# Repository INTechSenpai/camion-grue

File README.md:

# Après le [moon rover](https://intechsenpai.github.io/moon-rover/), INTech Senpaï est fier de vous présenter son camion grue !

## INTech Senpaï

INTech Senpaï participe pour la troisième fois à la Coupe de France de Robotique. Après le succès du robot sumo et du moon rover, qui a fini 29e à la coupe 2017, nous revenons en force avec le camion grue.

## Un modèle réduit unique

Notre camion grue est un modèle réduit à l'échelle 1:16 des immenses engins qui ont bercé notre enfance. À taille réelle, il mesurerait 3×7m ! Son design avec ses six roues (dont quatre directrices et motrices), ses feux de recul, de stop, de nuit, ses clignotants, ses gyrophare, sa grue est unique : il a été entièrement conçu par notre équipe.

## Un engin de chantier autonome

Notre camion grue utilise le système Kraken de déplacement autonome, fruit de plus de trois ans de R&D d'un doctorant en intelligence artificielle. Contrairement aux voitures autonomes qui suivent simplement une route, les engins de chantier évoluent dans un environnement encombré et changeant ; trouver un chemin implique un grand nombre de manœuvres qui peuvent être difficiles à trouver, même pour un humain. C'est ce que réalise le système Kraken, qui permet au camion grue de se déplacer avec aisance sur la table de jeu qui représente assez bien ce type d'environnement.

Le système Kraken est un logiciel libre et en [libre accès](https://github.com/PFGimenez/The-Kraken-Pathfinding).

## Un concurrent à la Coupe de France

Enfin, le camion grue est également un compétiteur de la Coupe. Sa grue terminée par une pince lui permet de manipuler des cubes et de les empiler.

## Hardware

Le camion grue est équipé de quatre unités de calcul : trois Teensy pour le contrôle bas niveau et une Raspberry Pi 3+ pour Kraken. Avec ses treize capteurs _time of flight_ dont deux rotatifs, il voit tout son environnement.

On peut voir très bien un capteur _time of flight_ au centre de l'image suivante :

Le camion grue peut facilement être ouvert afin d'accéder à son électronique.

Voici une partie de l'électronique du camion. On y voit les radiateurs des ponts en H (au centre), ainsi que deux Teensy (en bas à gauche) et la Raspberry Pi (en bas). L'autre partie de l'électronique se trouve dans la grue.

## L'équipe

[Sylvain Gaultier](https://github.com/sylvaing19) est le fondateur d'INTech Senpaï, il s'occupe de la conception et de la réalisation de la mécanique et de l'électronique du camion grue. Il a également programmé les trois Teensy.

[Pierre-François Gimenez](https://github.com/PFGimenez), doctorant en intelligence artificielle, a été recruté par Sylvain pour son projet de développement d'un camion grue autonome. Il est le concepteur et le programmeur du système Kraken.

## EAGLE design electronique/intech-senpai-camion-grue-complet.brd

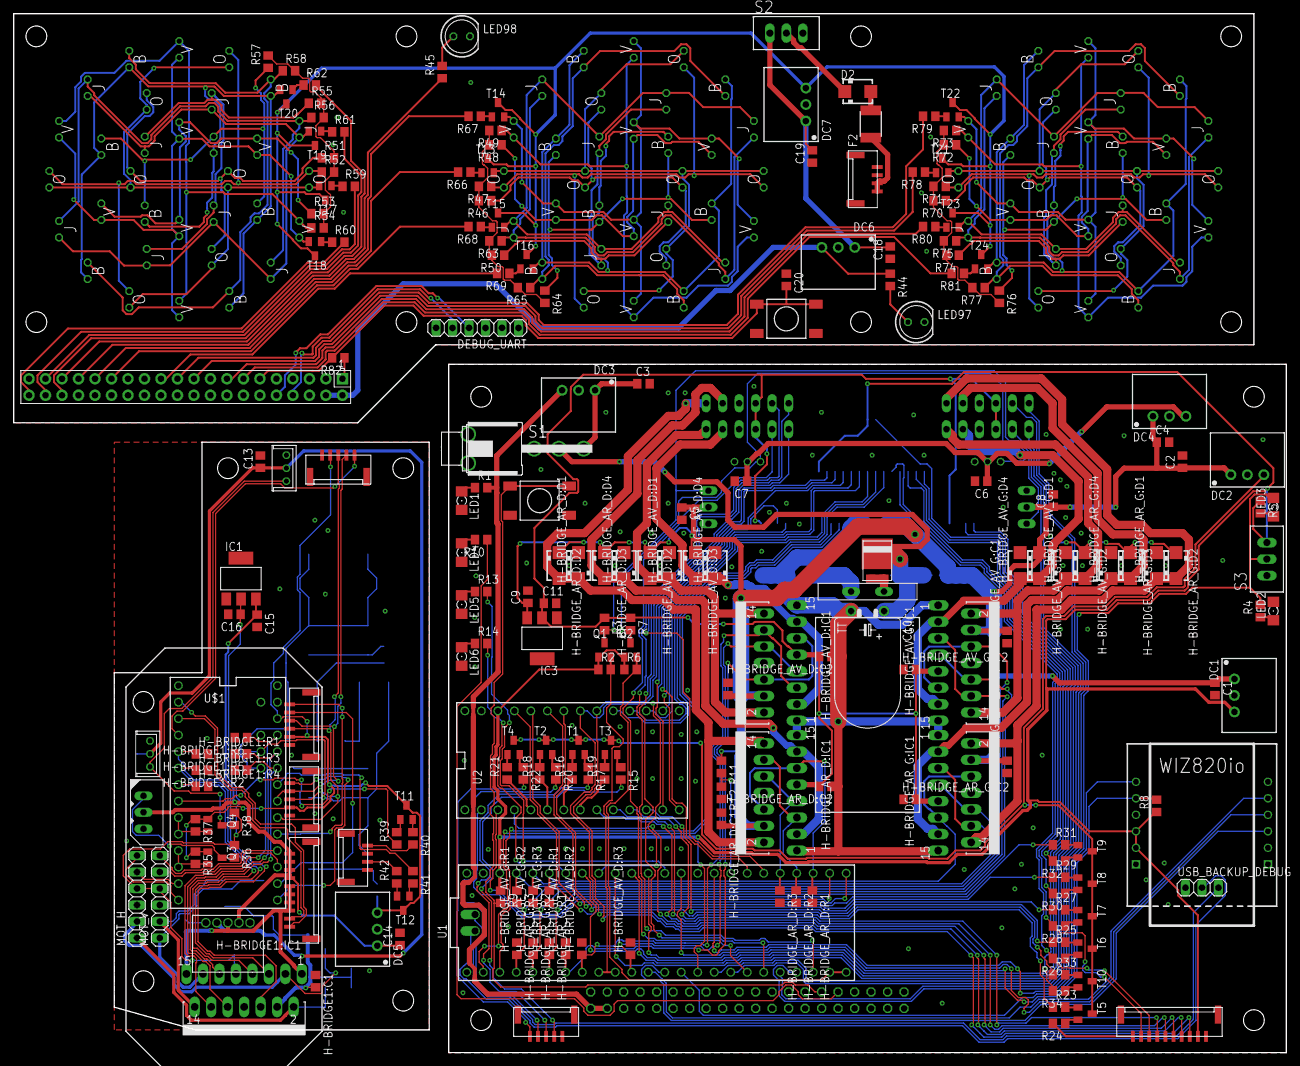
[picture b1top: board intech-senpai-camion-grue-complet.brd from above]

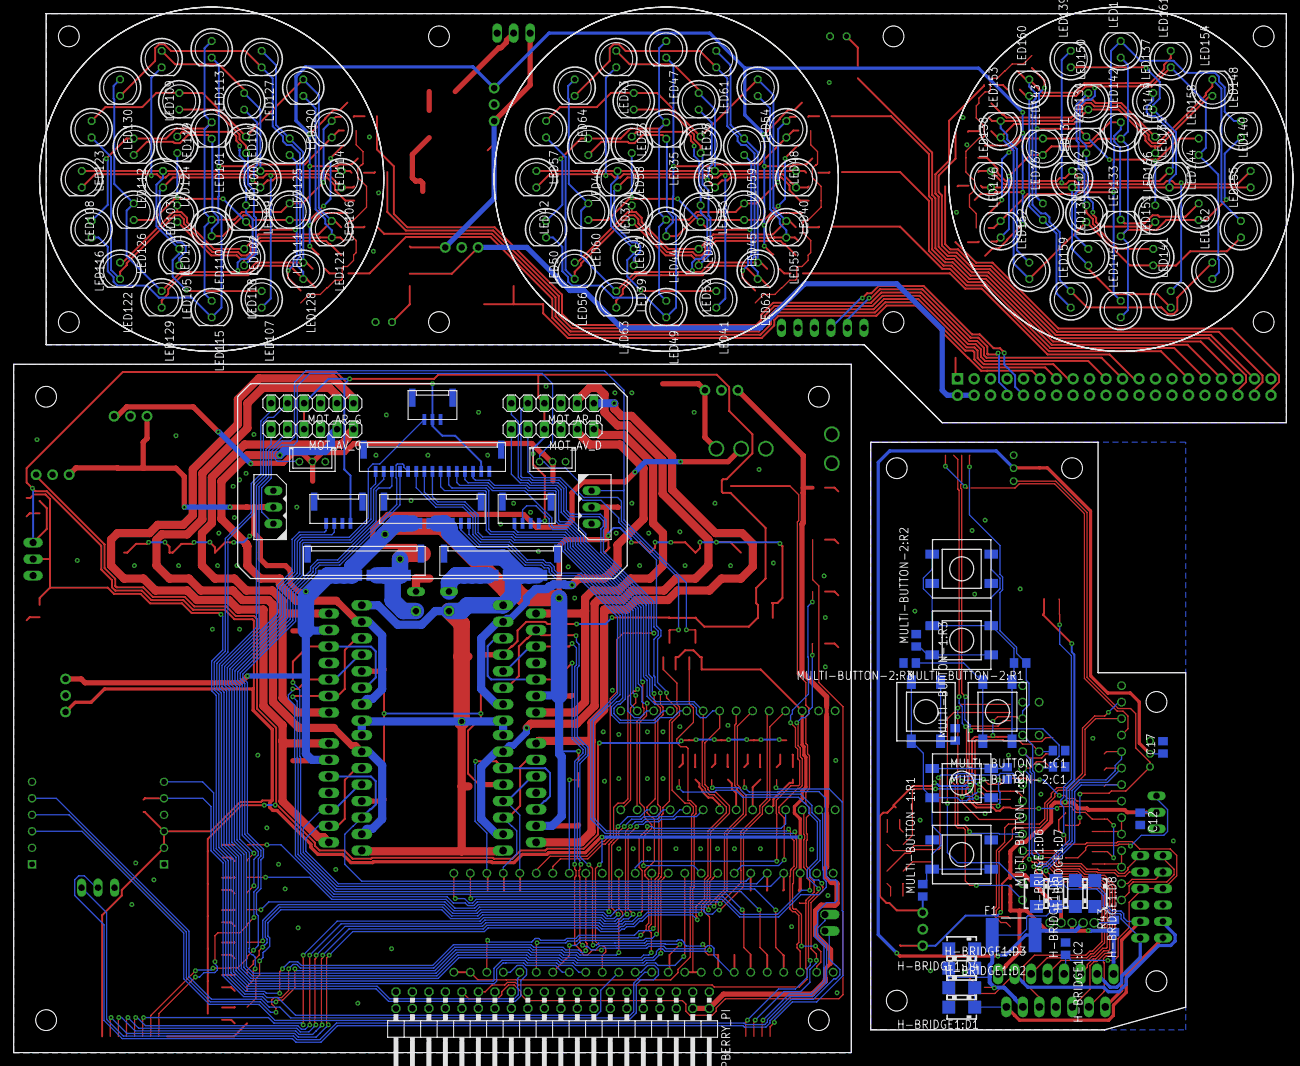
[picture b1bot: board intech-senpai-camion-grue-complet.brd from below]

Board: 2 copper layers, 196.0 x 160.0 mm, 361 parts (139 on the bottom side), 243 nets.

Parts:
ARRET_URGENCE: JST-12; GH-12-V
AX12_D, AX12_G, AX12_G1: DYNAMIXEL-1X03AX; DYNAMIXEL_AX_1X03
C1, C2, C3, C4, C9, C14, C15, C18, C19, C20: 10µF; C0805
C5, C6, C7, C8, C12, C13, C17: 1µF; C0805
C10: 4700µF; TT5D11L
C11, C16: 22µF; C0805
D1: DIODE_S15P45; TO-277A
D2: S1M; SMA
DC1, DC2, DC5, DC7: R-78C3.3-1.0; SIP3
DC3, DC6: R-78C5.0-1.0; SIP3
DC4: R-78C9.0-1.0; SIP3
DC-DC-6V: DC-DC-CONVERTER
DEBUG_UART: 1X06
DELS_ET_TOF_AR: JST-15; GH-15-V
DEL_GYRO: JST-05; GH-05-V
ENCODEUR_DROIT: JST-04GH-V; GH-04-V
ENCODEUR_GAUCHE: JST-04GH-V; GH-04-V
F1: MF-LSMF300
F2: MF-MSMF110
GRUE, GRUE1: JST-10; GH-10-V
GYRO: JST-04GH-V; GH-04-V
H-BRIDGE1:C1, H-BRIDGE1:C2: 100nF; C0805
H-BRIDGE1:D1, H-BRIDGE1:D2, H-BRIDGE1:D3, H-BRIDGE1:D4, H-BRIDGE1:D5, H-BRIDGE1:D6, H-BRIDGE1:D7, H-BRIDGE1:D8: S1M; SMA
H-BRIDGE1:IC1: L298; MULTIWATT-15
H-BRIDGE1:R1, H-BRIDGE1:R2, H-BRIDGE1:R3, H-BRIDGE1:R4, H-BRIDGE1:R5, H-BRIDGE1:R6: 10k; R0805
H-BRIDGE_AR_D:C1, H-BRIDGE_AR_D:C2: 100nF; C0805
H-BRIDGE_AR_D:D1, H-BRIDGE_AR_D:D2, H-BRIDGE_AR_D:D3, H-BRIDGE_AR_D:D4: S1M; SMA
H-BRIDGE_AR_D:IC1: L298; MULTIWATT-15
H-BRIDGE_AR_D:R1, H-BRIDGE_AR_D:R2, H-BRIDGE_AR_D:R3: 10k; R0805
H-BRIDGE_AR_G:C1, H-BRIDGE_AR_G:C2: 100nF; C0805
H-BRIDGE_AR_G:D1, H-BRIDGE_AR_G:D2, H-BRIDGE_AR_G:D3, H-BRIDGE_AR_G:D4: S1M; SMA
H-BRIDGE_AR_G:IC1: L298; MULTIWATT-15
H-BRIDGE_AR_G:R1, H-BRIDGE_AR_G:R2, H-BRIDGE_AR_G:R3: 10k; R0805
H-BRIDGE_AV_D:C1, H-BRIDGE_AV_D:C2: 100nF; C0805
H-BRIDGE_AV_D:D1, H-BRIDGE_AV_D:D2, H-BRIDGE_AV_D:D3, H-BRIDGE_AV_D:D4: S1M; SMA
H-BRIDGE_AV_D:IC1: L298; MULTIWATT-15
H-BRIDGE_AV_D:R1, H-BRIDGE_AV_D:R2, H-BRIDGE_AV_D:R3: 10k; R0805
H-BRIDGE_AV_G:C1, H-BRIDGE_AV_G:C2: 100nF; C0805
H-BRIDGE_AV_G:D1, H-BRIDGE_AV_G:D2, H-BRIDGE_AV_G:D3, H-BRIDGE_AV_G:D4: S1M; SMA
H-BRIDGE_AV_G:IC1: L298; MULTIWATT-15
H-BRIDGE_AV_G:R1, H-BRIDGE_AV_G:R2, H-BRIDGE_AV_G:R3: 10k; R0805
IC1, IC3: REG1117; SOT223
JUMPER: JST-03; GH-03-V
LED1, LED5: blue; 1206
LED2: green; 1206
LED3: orange; 1206
LED4, LED6: red; 1206
LED33, LED37, LED38, LED39, LED40, LED41, LED42, LED43, LED99, LED103, LED104, LED105, LED106, LED107, LED108, LED109, LED131, LED135, LED136, LED137, LED138, LED139, LED140, LED141: orange; LED5MM
LED34, LED51, LED52, LED53, LED54, LED55, LED56, LED57, LED100, LED117, LED118, LED119, LED120, LED121, LED122, LED123, LED132, LED149, LED150, LED151, LED152, LED153, LED154, LED155: jaune; LED5MM
LED35, LED44, LED45, LED46, LED47, LED48, LED49, LED50, LED97, LED101, LED110, LED111, LED112, LED113, LED114, LED115, LED116, LED133, LED142, LED143, LED144, LED145, LED146, LED147, LED148: vert; LED5MM
LED36, LED58, LED59, LED60, LED61, LED62, LED63, LED64, LED98, LED102, LED124, LED125, LED126, LED127, LED128, LED129, LED130, LED134, LED156, LED157, LED158, LED159, LED160, LED161, LED162: bleu; LED5MM
LIPO: JST-12; GH-12-V
LIPO1: JST-04GH-V; GH-04-V
MOT_AR_D: 1X06
MOT_AR_G: 1X06
MOT_AV_D: 1X06
MOT_AV_G: 1X06
MOT_H: 1X06
MOT_V: 1X06
MULTI-BUTTON-1:C1, MULTI-BUTTON-2:C1: 1µF; C0805
MULTI-BUTTON-1:R1, MULTI-BUTTON-2:R1: 4k7; R0805
MULTI-BUTTON-1:R2, MULTI-BUTTON-2:R2: 2k2; R0805
MULTI-BUTTON-1:R3, MULTI-BUTTON-2:R3: 10k; R0805
MULTI-BUTTON-1:U1, MULTI-BUTTON-1:U2, MULTI-BUTTON-1:U3, MULTI-BUTTON-2:U1, MULTI-BUTTON-2:U2, MULTI-BUTTON-2:U3: PUSH-BUTTON
P1: RGEF800; 5MM
PHARES_ET_TOF_AV: JST-10; GH-10-V
Q1, Q2, Q3, Q4: BSS138; SOT23
R1, R45: 470; R0805
R2, R3, R6, R7, R8, R9, R35, R36, R37, R38: 10k; R0805
R4, R5, R10, R13, R14: 330; R0805
R11: 22k; R0805
R12: 6k8; R0805
R15, R17, R20, R22, R24, R26, R28, R30, R32, R34, R40, R42, R46, R47, R48, R49, R50, R51, R52, R53, R54, R55, R56, R57, R58, R63, R64, R65, R70, R71, R72, R73, R74, R75, R76, R77: 0; R0805
R16, R18, R19, R21, R23, R25, R27, R29, R31, R33, R39, R41, R59, R60, R61, R62, R66, R67, R68, R69, R78, R79, R80, R81: 270; R0805
R43: 220; R0805
R44, R82: 1k; R0805
RASPPBERRY_PI: 2X20/90
RPI: RPI-ZERO; RASPBERRYPI_BASTELSTUBE_V13_RASPI_BOARD_B+_FULL
S1: SWITCH_LPV-1
S2, S3: TL36PO; TL3XPO
T1, T2, T3, T4, T5, T6, T7, T8, T9, T10, T11, T12, T13, T14, T15, T16, T17, T18, T19, T20, T21, T22, T23, T24: SOT23-BEC
TOF_LP_D_AND_DISPLAY: JST-05; GH-05-V
TOF_LP_G: JST-05; GH-05-V
TOF_PINCE: JST-06; GH-06-V
U1: TEENSY_3.5_DIL+USB
U2: TEENSY_3.1-3.2_DIL; TEENSY_3.0-3.2&LC_DIL
U$1: TEENSY_3.1-3.2_DIL+4; TEENSY_3.0-3.2&LC_DIL+4
U$2, U$4: PUSH-BUTTON
U$3: WIZ820IO; WIZ820
USB_BACKUP_DEBUG: 1X03
XL320_D, XL320_G, XL320_G1, XL320_G2: DYNAMIXEL-1X03XL; DYNAMIXEL_XL_1X03

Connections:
3V3@1: R82.1, RPI.1
12V_AUX: C3.1, DC3.1, S1.3
+3V3: DC1.3, DELS_ET_TOF_AR.2, JUMPER.2, PHARES_ET_TOF_AV.2, Q1.1, Q2.1, R2.1, R5.1, R6.1, R8.1, R9.1, S3.3, U1.3.3V, U1.3.3V3, U2.3.3V, U$3.VIN1, U$3.VIN2
+3V3G: DC5.3, MULTI-BUTTON-1:R1.1, MULTI-BUTTON-2:R1.1, Q3.1, Q4.1, R35.1, R37.1, T11.C, T12.C, TOF_LP_D_AND_DISPLAY.2, TOF_LP_G.2, TOF_PINCE.2, U$1.3.3V
+3V3_LEDS: DC2.3, T1.C, T2.C, T3.C, T4.C, T5.C, T6.C, T7.C, T8.C, T9.C, T10.C
+5V: C11.1, ENCODEUR_DROIT.1, ENCODEUR_GAUCHE.1, H-BRIDGE_AR_D:C2.2, H-BRIDGE_AR_D:IC1.9, H-BRIDGE_AR_G:C2.2, H-BRIDGE_AR_G:IC1.9, H-BRIDGE_AV_D:C2.2, H-BRIDGE_AV_D:IC1.9, H-BRIDGE_AV_G:C2.2, H-BRIDGE_AV_G:IC1.9, IC3.2, MOT_AR_D.4, MOT_AR_G.4, MOT_AV_D.4, MOT_AV_G.4, R3.1, R7.1
+5VB: DC6.3, R44.1, RPI.2, RPI.4
+5VG: C16.1, H-BRIDGE1:C2.2, H-BRIDGE1:IC1.9, IC1.2, MOT_H.4, MOT_V.4, R36.1, R38.1
+5V_RPI: DC3.3, R1.2, RASPPBERRY_PI.2, RASPPBERRY_PI.4
+6V: C13.1, C17.1, DC-DC-6V.VOUT, F1.2, XL320_G1.VCC, XL320_G2.VCC
+6V5: C6.1, C7.1, DC4.3, XL320_D.VCC, XL320_G.VCC
+12V: ARRET_URGENCE.7, ARRET_URGENCE.8, ARRET_URGENCE.9, ARRET_URGENCE.10, ARRET_URGENCE.11, ARRET_URGENCE.12, AX12_D.DYN_VCC, AX12_G.DYN_VCC, C1.1, C2.1, C4.1, C5.1, C8.1, C9.1, DC1.1, DC2.1, DC4.1, GRUE.7, GRUE.8, GRUE.9, GRUE.10, H-BRIDGE_AR_D:C1.2, H-BRIDGE_AR_D:D2.C, H-BRIDGE_AR_D:D3.C, H-BRIDGE_AR_D:IC1.4, H-BRIDGE_AR_G:C1.2, H-BRIDGE_AR_G:D2.C, H-BRIDGE_AR_G:D3.C, H-BRIDGE_AR_G:IC1.4, H-BRIDGE_AV_D:C1.2, H-BRIDGE_AV_D:D2.C, H-BRIDGE_AV_D:D3.C, H-BRIDGE_AV_D:IC1.4, H-BRIDGE_AV_G:C1.2, H-BRIDGE_AV_G:D2.C, H-BRIDGE_AV_G:D3.C, H-BRIDGE_AV_G:IC1.4, IC3.3, R11.1
+12VB: C18.2, C19.2, DC6.1, DC7.1, S2.1
+12VG: AX12_G1.DYN_VCC, C12.1, C14.1, C15.1, DC5.1, DC-DC-6V.VIN, GRUE1.7, GRUE1.8, GRUE1.9, GRUE1.10, IC1.3
CHOOSE_COLOR: LED3.C, R4.2, S3.2, U1.A22
DEL_BLEU_1: LED134.A, LED156.A, LED157.A, LED158.A, LED159.A, LED160.A, LED161.A, LED162.A, T20.E
DEL_BLEU_1_PWM: R62.2, RPI.36
DEL_BLEU_2: LED36.A, LED58.A, LED59.A, LED60.A, LED61.A, LED62.A, LED63.A, LED64.A, T16.E
DEL_BLEU_2_PWM: R69.2, RPI.23
DEL_BLEU_3: LED102.A, LED124.A, LED125.A, LED126.A, LED127.A, LED128.A, LED129.A, LED130.A, T24.E
DEL_BLEU_3_PWM: R81.2, RPI.13
DEL_CLIGNOTANT_D: DELS_ET_TOF_AR.11, PHARES_ET_TOF_AV.9, R28.2
DEL_CLIGNOTANT_D_PWM: R27.1, U2.20/A6
DEL_CLIGNOTANT_G: DELS_ET_TOF_AR.12, PHARES_ET_TOF_AV.8, R26.2
DEL_CLIGNOTANT_G_PWM: R25.1, U2.10
DEL_FEUX_NUIT_AR: DELS_ET_TOF_AR.13, R30.2
DEL_FEUX_NUIT_AR_PWM: R29.1, U2.21/A7
DEL_FEUX_NUIT_AV: PHARES_ET_TOF_AV.10, R24.2
DEL_FEUX_NUIT_AV_PWM: R23.1, U2.9
DEL_FEUX_RECUL: DELS_ET_TOF_AR.15, R34.2
DEL_FEUX_RECUL_PWM: R33.1, U2.23/A9
DEL_FEUX_STOP: DELS_ET_TOF_AR.14, R32.2
DEL_FEUX_STOP_PWM: R31.1, U2.22/A8
DEL_GYRO_1: DEL_GYRO.2, R15.2
DEL_GYRO_1G: GYRO.1, R40.2
DEL_GYRO_1_PWM: R19.1, U2.6
DEL_GYRO_1_PWMG: R39.1, U$1.6
DEL_GYRO_2: DEL_GYRO.3, R17.2
DEL_GYRO_2G: GYRO.3, R42.2
DEL_GYRO_2_PWM: R16.1, U2.5
DEL_GYRO_2_PWMG: R41.1, U$1.20/A6
DEL_GYRO_3: DEL_GYRO.4, R20.2
DEL_GYRO_3_PWM: R18.1, U2.4
DEL_GYRO_4: DEL_GYRO.5, R22.2
DEL_GYRO_4_PWM: R21.1, U2.3
DEL_JAUNE_1: LED132.A, LED149.A, LED150.A, LED151.A, LED152.A, LED153.A, LED154.A, LED155.A, T19.E
DEL_JAUNE_1_PWM: R61.2, RPI.37
DEL_JAUNE_2: LED34.A, LED51.A, LED52.A, LED53.A, LED54.A, LED55.A, LED56.A, LED57.A, T15.E
DEL_JAUNE_2_PWM: R68.2, RPI.29
DEL_JAUNE_3: LED100.A, LED117.A, LED118.A, LED119.A, LED120.A, LED121.A, LED122.A, LED123.A, T23.E
DEL_JAUNE_3_PWM: R80.2, RPI.15
DEL_ORANGE_1: LED131.A, LED135.A, LED136.A, LED137.A, LED138.A, LED139.A, LED140.A, LED141.A, T17.E
DEL_ORANGE_1_PWM: R59.2, RPI.38
DEL_ORANGE_2: LED33.A, LED37.A, LED38.A, LED39.A, LED40.A, LED41.A, LED42.A, LED43.A, T13.E
DEL_ORANGE_2_PWM: R66.2, RPI.31
DEL_ORANGE_3: LED99.A, LED103.A, LED104.A, LED105.A, LED106.A, LED107.A, LED108.A, LED109.A, T21.E
DEL_ORANGE_3_PWM: R78.2, RPI.19
DEL_POWER: DC7.3, T13.C, T14.C, T15.C, T16.C, T17.C, T18.C, T19.C, T20.C, T21.C, T22.C, T23.C, T24.C
DEL_VERT_1: LED133.A, LED142.A, LED143.A, LED144.A, LED145.A, LED146.A, LED147.A, LED148.A, T18.E
DEL_VERT_1_PWM: R60.2, RPI.40
DEL_VERT_2: LED35.A, LED44.A, LED45.A, LED46.A, LED47.A, LED48.A, LED49.A, LED50.A, T14.E
DEL_VERT_2_PWM: R67.2, RPI.33
DEL_VERT_3: LED101.A, LED110.A, LED111.A, LED112.A, LED113.A, LED114.A, LED115.A, LED116.A, T22.E
DEL_VERT_3_PWM: R79.2, RPI.21
ENC_AR_D_A: MOT_AR_D.5, U1.30
ENC_AR_D_B: MOT_AR_D.6, U1.38/A19
ENC_AR_G_A: MOT_AR_G.5, U1.28
ENC_AR_G_B: MOT_AR_G.6, U1.29
ENC_AV_D_A: MOT_AV_D.5, U1.26
ENC_AV_D_B: MOT_AV_D.6, U1.27
ENC_AV_G_A: MOT_AV_G.5, U1.24
ENC_AV_G_B: MOT_AV_G.6, U1.25
ENC_D_A: ENCODEUR_DROIT.3, U1.18/A4
ENC_D_B: ENCODEUR_DROIT.4, U1.39/A20
ENC_G_A: ENCODEUR_GAUCHE.3, U1.16/A2
ENC_G_B: ENCODEUR_GAUCHE.4, U1.17/A3
ETH_MISO: U1.12, U$3.MISO
ETH_MOSI: U1.11, U$3.MOSI
ETH_RST: R8.2, U1.15/A1, U$3.RESET
ETH_SCLK: U1.13, U$3.SCLK
ETH_SS: U1.10, U$3.SS
GND: AX12_D.GND, AX12_G.GND, C1.2, C2.2, C3.2, C4.2, C5.2, C6.2, C7.2, C8.2, C9.2, C10.-, C11.2, DC1.2, DC2.2, DC3.2, DC4.2, DELS_ET_TOF_AR.1, DEL_GYRO.1, ENCODEUR_DROIT.2, ENCODEUR_GAUCHE.2, GRUE.3, GRUE.4, GRUE.5, GRUE.6, H-BRIDGE_AR_D:C1.1, H-BRIDGE_AR_D:C2.1, H-BRIDGE_AR_D:D1.A, H-BRIDGE_AR_D:D4.A, H-BRIDGE_AR_D:IC1.1, H-BRIDGE_AR_D:IC1.8, H-BRIDGE_AR_D:IC1.15, H-BRIDGE_AR_D:R1.2, H-BRIDGE_AR_D:R2.2, H-BRIDGE_AR_D:R3.2, H-BRIDGE_AR_G:C1.1, H-BRIDGE_AR_G:C2.1, H-BRIDGE_AR_G:D1.A, H-BRIDGE_AR_G:D4.A, H-BRIDGE_AR_G:IC1.1, H-BRIDGE_AR_G:IC1.8, H-BRIDGE_AR_G:IC1.15, H-BRIDGE_AR_G:R1.2, H-BRIDGE_AR_G:R2.2, H-BRIDGE_AR_G:R3.2, H-BRIDGE_AV_D:C1.1, H-BRIDGE_AV_D:C2.1, H-BRIDGE_AV_D:D1.A, H-BRIDGE_AV_D:D4.A, H-BRIDGE_AV_D:IC1.1, H-BRIDGE_AV_D:IC1.8, H-BRIDGE_AV_D:IC1.15, H-BRIDGE_AV_D:R1.2, H-BRIDGE_AV_D:R2.2, H-BRIDGE_AV_D:R3.2, H-BRIDGE_AV_G:C1.1, H-BRIDGE_AV_G:C2.1, H-BRIDGE_AV_G:D1.A, H-BRIDGE_AV_G:D4.A, H-BRIDGE_AV_G:IC1.1, H-BRIDGE_AV_G:IC1.8, H-BRIDGE_AV_G:IC1.15, H-BRIDGE_AV_G:R1.2, H-BRIDGE_AV_G:R2.2, H-BRIDGE_AV_G:R3.2, IC3.1, JUMPER.1, LED1.C, LED2.C, LED4.C, LED5.C, LED6.C, LIPO.1, LIPO.2, LIPO.3, LIPO.4, LIPO.5, LIPO.6, MOT_AR_D.3, MOT_AR_G.3, MOT_AV_D.3, MOT_AV_G.3, PHARES_ET_TOF_AV.1, R12.2, RASPPBERRY_PI.6, RASPPBERRY_PI.9, RASPPBERRY_PI.14, RASPPBERRY_PI.20, RASPPBERRY_PI.25, RASPPBERRY_PI.30, RASPPBERRY_PI.34, RASPPBERRY_PI.39, S1.B, S1.B1, S3.1, U1.AGND, U1.GND, U1.GND1, U2.AGND, U2.GND, U$2.1, U$2.2, U$3.GND1, U$3.GND2, U$3.GND3, U$3.PWDN, USB_BACKUP_DEBUG.1, XL320_D.GND, XL320_G.GND
GNDB: C18.1, C19.1, C20.1, DC6.2, DC7.2, DEBUG_UART.1, LED97.K, LED98.K, LIPO1.1, LIPO1.2, R46.2, R47.2, R48.2, R49.2, R50.2, R51.2, R52.2, R53.2, R54.2, R55.2, R56.2, R57.2, R58.2, R63.2, R64.2, R65.2, R70.2, R71.2, R72.2, R73.2, R74.2, R75.2, R76.2, R77.2, RPI.6, RPI.9, RPI.14, RPI.20, RPI.25, RPI.30, RPI.34, RPI.39, U$4.3, U$4.4
GNDG: AX12_G1.GND, C12.2, C13.2, C14.2, C15.2, C16.2, C17.2, DC5.2, DC-DC-6V.GND, GRUE1.3, GRUE1.4, GRUE1.5, GRUE1.6, GYRO.2, GYRO.4, H-BRIDGE1:C1.1, H-BRIDGE1:C2.1, H-BRIDGE1:D1.A, H-BRIDGE1:D4.A, H-BRIDGE1:D5.A, H-BRIDGE1:D8.A, H-BRIDGE1:IC1.1, H-BRIDGE1:IC1.8, H-BRIDGE1:IC1.15, H-BRIDGE1:R1.2, H-BRIDGE1:R2.2, H-BRIDGE1:R3.2, H-BRIDGE1:R4.2, H-BRIDGE1:R5.2, H-BRIDGE1:R6.2, IC1.1, MOT_H.3, MOT_V.3, MULTI-BUTTON-1:C1.1, MULTI-BUTTON-1:R2.2, MULTI-BUTTON-1:R3.2, MULTI-BUTTON-1:U3.3, MULTI-BUTTON-1:U3.4, MULTI-BUTTON-2:C1.1, MULTI-BUTTON-2:R2.2, MULTI-BUTTON-2:R3.2, MULTI-BUTTON-2:U3.3, MULTI-BUTTON-2:U3.4, R43.1, TOF_LP_D_AND_DISPLAY.1, TOF_LP_G.1, TOF_PINCE.1, U$1.AGND, U$1.GND, XL320_G1.GND, XL320_G2.GND
GRUE_SERIAL_MISO: GRUE.2, U1.0
GRUE_SERIAL_MISOG: GRUE1.2, U$1.1
GRUE_SERIAL_MOSI: GRUE.1, U1.1
GRUE_SERIAL_MOSIG: GRUE1.1, U$1.0
JUMPER: JUMPER.3, U1.19/A5
MOT_AR_D_EN: H-BRIDGE_AR_D:IC1.6, H-BRIDGE_AR_D:IC1.11, H-BRIDGE_AR_D:R1.1, U1.35/A16
MOT_AR_D_IN1: H-BRIDGE_AR_D:IC1.5, H-BRIDGE_AR_D:IC1.12, H-BRIDGE_AR_D:R2.1, U1.36/A17
MOT_AR_D_IN2: H-BRIDGE_AR_D:IC1.7, H-BRIDGE_AR_D:IC1.10, H-BRIDGE_AR_D:R3.1, U1.37/A18
MOT_AR_D_OUT+: H-BRIDGE_AR_D:D1.C, H-BRIDGE_AR_D:D2.A, H-BRIDGE_AR_D:IC1.2, H-BRIDGE_AR_D:IC1.14, MOT_AR_D.1
MOT_AR_D_OUT-: H-BRIDGE_AR_D:D3.A, H-BRIDGE_AR_D:D4.C, H-BRIDGE_AR_D:IC1.3, H-BRIDGE_AR_D:IC1.13, MOT_AR_D.2
MOT_AR_G_EN: H-BRIDGE_AR_G:IC1.6, H-BRIDGE_AR_G:IC1.11, H-BRIDGE_AR_G:R1.1, U1.21/A7
MOT_AR_G_IN1: H-BRIDGE_AR_G:IC1.5, H-BRIDGE_AR_G:IC1.12, H-BRIDGE_AR_G:R2.1, U1.22/A8
MOT_AR_G_IN2: H-BRIDGE_AR_G:IC1.7, H-BRIDGE_AR_G:IC1.10, H-BRIDGE_AR_G:R3.1, U1.23/A9
MOT_AR_G_OUT+: H-BRIDGE_AR_G:D1.C, H-BRIDGE_AR_G:D2.A, H-BRIDGE_AR_G:IC1.2, H-BRIDGE_AR_G:IC1.14, MOT_AR_G.1
MOT_AR_G_OUT-: H-BRIDGE_AR_G:D3.A, H-BRIDGE_AR_G:D4.C, H-BRIDGE_AR_G:IC1.3, H-BRIDGE_AR_G:IC1.13, MOT_AR_G.2
MOT_AV_D_EN: H-BRIDGE_AV_D:IC1.6, H-BRIDGE_AV_D:IC1.11, H-BRIDGE_AV_D:R1.1, U1.5
MOT_AV_D_IN1: H-BRIDGE_AV_D:IC1.5, H-BRIDGE_AV_D:IC1.12, H-BRIDGE_AV_D:R2.1, U1.6
MOT_AV_D_IN2: H-BRIDGE_AV_D:IC1.7, H-BRIDGE_AV_D:IC1.10, H-BRIDGE_AV_D:R3.1, U1.9
MOT_AV_D_OUT+: H-BRIDGE_AV_D:D1.C, H-BRIDGE_AV_D:D2.A, H-BRIDGE_AV_D:IC1.2, H-BRIDGE_AV_D:IC1.14, MOT_AV_D.1
MOT_AV_D_OUT-: H-BRIDGE_AV_D:D3.A, H-BRIDGE_AV_D:D4.C, H-BRIDGE_AV_D:IC1.3, H-BRIDGE_AV_D:IC1.13, MOT_AV_D.2
MOT_AV_G_EN: H-BRIDGE_AV_G:IC1.6, H-BRIDGE_AV_G:IC1.11, H-BRIDGE_AV_G:R1.1, U1.2
MOT_AV_G_IN1: H-BRIDGE_AV_G:IC1.5, H-BRIDGE_AV_G:IC1.12, H-BRIDGE_AV_G:R2.1, U1.3
MOT_AV_G_IN2: H-BRIDGE_AV_G:IC1.7, H-BRIDGE_AV_G:IC1.10, H-BRIDGE_AV_G:R3.1, U1.4
MOT_AV_G_OUT+: H-BRIDGE_AV_G:D1.C, H-BRIDGE_AV_G:D2.A, H-BRIDGE_AV_G:IC1.2, H-BRIDGE_AV_G:IC1.14, MOT_AV_G.1
MOT_AV_G_OUT-: H-BRIDGE_AV_G:D3.A, H-BRIDGE_AV_G:D4.C, H-BRIDGE_AV_G:IC1.3, H-BRIDGE_AV_G:IC1.13, MOT_AV_G.2
MOT_H_EN: H-BRIDGE1:IC1.6, H-BRIDGE1:R1.1, U$1.3
MOT_H_ENC_A: MOT_H.5, U$1.11
MOT_H_ENC_B: MOT_H.6, U$1.12
MOT_H_IN1: H-BRIDGE1:IC1.5, H-BRIDGE1:R3.1, U$1.4
MOT_H_IN2: H-BRIDGE1:IC1.7, H-BRIDGE1:R4.1, U$1.5
MOT_H_OUT+: H-BRIDGE1:D1.C, H-BRIDGE1:D2.A, H-BRIDGE1:IC1.2, MOT_H.1
MOT_H_OUT-: H-BRIDGE1:D3.A, H-BRIDGE1:D4.C, H-BRIDGE1:IC1.3, MOT_H.2
MOT_V_EN: H-BRIDGE1:IC1.11, H-BRIDGE1:R2.1, U$1.21/A7
MOT_V_ENC_A: MOT_V.5, U$1.15/A1
MOT_V_ENC_B: MOT_V.6, U$1.16/A2
MOT_V_IN1: H-BRIDGE1:IC1.10, H-BRIDGE1:R5.1, U$1.22/A8
MOT_V_IN2: H-BRIDGE1:IC1.12, H-BRIDGE1:R6.1, U$1.23/A9
MOT_V_OUT+: H-BRIDGE1:D5.C, H-BRIDGE1:D6.A, H-BRIDGE1:IC1.13, MOT_V.1
MOT_V_OUT-: H-BRIDGE1:D7.A, H-BRIDGE1:D8.C, H-BRIDGE1:IC1.14, MOT_V.2
MULTI-BUTTON-1:N$3: MULTI-BUTTON-1:R2.1, MULTI-BUTTON-1:U2.3, MULTI-BUTTON-1:U2.4
MULTI-BUTTON-1:N$4: MULTI-BUTTON-1:R3.1, MULTI-BUTTON-1:U1.3, MULTI-BUTTON-1:U1.4
MULTI-BUTTON-2:N$3: MULTI-BUTTON-2:R2.1, MULTI-BUTTON-2:U2.3, MULTI-BUTTON-2:U2.4
MULTI-BUTTON-2:N$4: MULTI-BUTTON-2:R3.1, MULTI-BUTTON-2:U1.3, MULTI-BUTTON-2:U1.4
unnamed: LED1.A, R1.1
unnamed: R9.2, RASPPBERRY_PI.29, U$2.3, U$2.4
unnamed: ARRET_URGENCE.1, ARRET_URGENCE.2, ARRET_URGENCE.3, ARRET_URGENCE.4, ARRET_URGENCE.5, ARRET_URGENCE.6, C10.+, D1.-, S1.2
unnamed: D1.+1, D1.+2, P1.P$1
unnamed: R10.1, RASPPBERRY_PI.31
unnamed: U1.33/A14, U2.0
unnamed: LED2.A, R4.1
unnamed: LED3.A, R5.2
unnamed: LIPO.7, LIPO.8, LIPO.9, LIPO.10, LIPO.11, LIPO.12, P1.P$2
unnamed: U1.34/A15, U2.1
unnamed: LED4.A, R10.2
unnamed: R11.2, R12.1, U1.A21
unnamed: LED6.A, R14.1
unnamed: LED5.A, R13.1
unnamed: R13.2, U1.14/A0
unnamed: R14.2, U1.20/A6
unnamed: R15.1, T3.E
unnamed: R19.2, T3.B
unnamed: R40.1, T11.E
unnamed: R39.2, T11.B
unnamed: R17.1, T1.E
unnamed: R16.2, T1.B
unnamed: R42.1, T12.E
unnamed: R41.2, T12.B
unnamed: R20.1, T2.E
unnamed: R18.2, T2.B
unnamed: DC-DC-6V.TRIM+, R43.2
unnamed: MULTI-BUTTON-1:C1.2, MULTI-BUTTON-1:R1.2, MULTI-BUTTON-1:U1.1, MULTI-BUTTON-1:U1.2, MULTI-BUTTON-1:U2.1, MULTI-BUTTON-1:U2.2, MULTI-BUTTON-1:U3.1, MULTI-BUTTON-1:U3.2, U$1.A10
unnamed: R22.1, T4.E
unnamed: R21.2, T4.B
unnamed: MULTI-BUTTON-2:C1.2, MULTI-BUTTON-2:R1.2, MULTI-BUTTON-2:U1.1, MULTI-BUTTON-2:U1.2, MULTI-BUTTON-2:U2.1, MULTI-BUTTON-2:U2.2, MULTI-BUTTON-2:U3.1, MULTI-BUTTON-2:U3.2, U$1.A11
unnamed: F1.1, H-BRIDGE1:C1.2, H-BRIDGE1:D2.C, H-BRIDGE1:D3.C, H-BRIDGE1:D6.C, H-BRIDGE1:D7.C, H-BRIDGE1:IC1.4
unnamed: R24.1, T5.E
unnamed: R23.2, T5.B
unnamed: F2.1, LIPO1.3, LIPO1.4
unnamed: D2.A, F2.2
unnamed: R26.1, T6.E
unnamed: R25.2, T6.B
unnamed: D2.C, S2.2
unnamed: LED97.A, R44.2
unnamed: R28.1, T7.E
unnamed: R27.2, T7.B
unnamed: LED98.A, R45.2
unnamed: LED33.K, LED37.K, LED38.K, LED39.K, R46.1
unnamed: R30.1, T8.E
unnamed: R29.2, T8.B
unnamed: LED40.K, LED41.K, LED42.K, LED43.K, R47.1
unnamed: LED35.K, LED44.K, LED45.K, LED46.K, R48.1
unnamed: R32.1, T9.E
unnamed: R31.2, T9.B
unnamed: LED47.K, LED48.K, LED49.K, LED50.K, R49.1
unnamed: LED34.K, LED51.K, LED52.K, LED53.K, R50.1
unnamed: R34.1, T10.E
unnamed: R33.2, T10.B
unnamed: LED131.K, LED135.K, LED136.K, LED137.K, R51.1
unnamed: LED138.K, LED139.K, LED140.K, LED141.K, R52.1
unnamed: LED133.K, LED142.K, LED143.K, LED144.K, R53.1
unnamed: LED145.K, LED146.K, LED147.K, LED148.K, R54.1
unnamed: LED132.K, LED149.K, LED150.K, LED151.K, R55.1
unnamed: LED152.K, LED153.K, LED154.K, LED155.K, R56.1
unnamed: LED134.K, LED156.K, LED157.K, LED158.K, R57.1
unnamed: LED159.K, LED160.K, LED161.K, LED162.K, R58.1
unnamed: R59.1, T17.B
unnamed: R60.1, T18.B
unnamed: R61.1, T19.B
unnamed: R62.1, T20.B
unnamed: LED54.K, LED55.K, LED56.K, LED57.K, R63.1
unnamed: LED36.K, LED58.K, LED59.K, LED60.K, R64.1
unnamed: LED61.K, LED62.K, LED63.K, LED64.K, R65.1
unnamed: R66.1, T13.B
unnamed: R67.1, T14.B
unnamed: R68.1, T15.B
unnamed: R69.1, T16.B
unnamed: LED99.K, LED103.K, LED104.K, LED105.K, R70.1
unnamed: LED106.K, LED107.K, LED108.K, LED109.K, R71.1
unnamed: LED101.K, LED110.K, LED111.K, LED112.K, R72.1
unnamed: LED113.K, LED114.K, LED115.K, LED116.K, R73.1
unnamed: LED100.K, LED117.K, LED118.K, LED119.K, R74.1
unnamed: LED120.K, LED121.K, LED122.K, LED123.K, R75.1
unnamed: LED102.K, LED124.K, LED125.K, LED126.K, R76.1
unnamed: LED127.K, LED128.K, LED129.K, LED130.K, R77.1
unnamed: R78.1, T21.B
unnamed: R79.1, T22.B
unnamed: R80.1, T23.B
unnamed: R81.1, T24.B
POWEROFF: C20.2, R82.2, RPI.11, U$4.1, U$4.2
RX: DEBUG_UART.4, RPI.10
SCL: DELS_ET_TOF_AR.4, PHARES_ET_TOF_AV.4, U2.19/A5
SCLG: TOF_LP_D_AND_DISPLAY.4, TOF_LP_G.4, TOF_PINCE.4, U$1.19/A5
SDA: DELS_ET_TOF_AR.3, PHARES_ET_TOF_AV.3, U2.18/A4
SDAG: TOF_LP_D_AND_DISPLAY.3, TOF_LP_G.3, TOF_PINCE.3, U$1.18/A4
SERIAL_AX12: Q1.2, R2.2, U1.7, U1.8
SERIAL_AX12G: Q3.2, R35.2, U$1.9, U$1.10
SERIAL_AX12_5V: AX12_D.DATA, AX12_G.DATA, Q1.3, R3.2
SERIAL_AX12_5VG: AX12_G1.DATA, Q3.3, R36.2
SERIAL_XL320: Q2.2, R6.2, U1.31/A12, U1.32/A13
SERIAL_XL320G: Q4.2, R37.2, U$1.7, U$1.8
SERIAL_XL320_5V: Q2.3, R7.2, XL320_D.DATA, XL320_G.DATA
SERIAL_XL320_5VG: Q4.3, R38.2, XL320_G1.DATA, XL320_G2.DATA
STATUS_LED: R45.1, RPI.35
TOF_AR_D: DELS_ET_TOF_AR.7, U2.14/A0
TOF_AR_G: DELS_ET_TOF_AR.8, U2.15/A1
TOF_AV: PHARES_ET_TOF_AV.6, U2.7
TOF_AV_D: PHARES_ET_TOF_AV.7, U2.8
TOF_AV_G: PHARES_ET_TOF_AV.5, U2.2
TOF_FLAN_AR_D: DELS_ET_TOF_AR.6, U2.12
TOF_FLAN_AR_G: DELS_ET_TOF_AR.9, U2.16/A2
TOF_FLAN_AV_D: DELS_ET_TOF_AR.5, U2.11
TOF_FLAN_AV_G: DELS_ET_TOF_AR.10, U2.17/A3
TOF_LP_D: TOF_LP_D_AND_DISPLAY.5, U$1.13
TOF_LP_G: TOF_LP_G.5, U$1.2
TOF_PINCE_EXT: TOF_PINCE.6, U$1.17/A3
TOF_PINCE_INT: TOF_PINCE.5, U$1.14/A0
TX: DEBUG_UART.5, RPI.8
USB_D+: U1.USBD+, USB_BACKUP_DEBUG.2
USB_D-: U1.USBD-, USB_BACKUP_DEBUG.3

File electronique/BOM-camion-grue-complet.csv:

Qty;Value;Device;Package;Parts;Description;RS
8;;BC817-16-NPN-SOT23-BEC;SOT23-BEC;T2, T4, T5, T6, T7, T8, T9, T10;NPN Transistror;
16;;BC817-16-NPN-SOT23-BEC;SOT23-BEC;T1, T3, T11, T12, T13, T14, T15, T16, T17, T18, T19, T20, T21, T22, T23, T24;NPN Transistror;781-4272
1;;PINHD-1X3;1X03;USB_BACKUP_DEBUG;PIN HEADER;
7;;PINHD-1X6;1X06;DEBUG_UART, MOT_AR_D, MOT_AR_G, MOT_AV_D, MOT_AV_G, MOT_H, MOT_V;PIN HEADER;
1;;PINHD-2X20/90;2X20/90;RASPPBERRY_PI;PIN HEADER;
1;;SWITCH_LPV-1;SWITCH_LPV-1;S1;TOGGLE SWITCH;734-7306
36;0;R-EU_R0805;R0805;R15, R17, R20, R22, R24, R26, R28, R30, R32, R34, R40, R42, R46, R47, R48, R49, R50, R51, R52, R53, R54, R55, R56, R57, R58, R63, R64, R65, R70, R71, R72, R73, R74, R75, R76, R77;RESISTOR, European symbol;
10;100nF;C-EUC0805;C0805;H-BRIDGE1:C1, H-BRIDGE1:C2, H-BRIDGE_AR_D:C1, H-BRIDGE_AR_D:C2, H-BRIDGE_AR_G:C1, H-BRIDGE_AR_G:C2, H-BRIDGE_AV_D:C1, H-BRIDGE_AV_D:C2, H-BRIDGE_AV_G:C1, H-BRIDGE_AV_G:C2;CAPACITOR, European symbol;
30;10k;R-EU_R0805;R0805;H-BRIDGE1:R1, H-BRIDGE1:R2, H-BRIDGE1:R3, H-BRIDGE1:R4, H-BRIDGE1:R5, H-BRIDGE1:R6, H-BRIDGE_AR_D:R1, H-BRIDGE_AR_D:R2, H-BRIDGE_AR_D:R3, H-BRIDGE_AR_G:R1, H-BRIDGE_AR_G:R2, H-BRIDGE_AR_G:R3, H-BRIDGE_AV_D:R1, H-BRIDGE_AV_D:R2, H-BRIDGE_AV_D:R3, H-BRIDGE_AV_G:R1, H-BRIDGE_AV_G:R2, H-BRIDGE_AV_G:R3, MULTI-BUTTON-1:R3, MULTI-BUTTON-2:R3, R2, R3, R6, R7, R8, R9, R35, R36, R37, R38;RESISTOR, European symbol;
10;10µF;C-EUC0805;C0805;C1, C2, C3, C4, C9, C14, C15, C18, C19, C20;CAPACITOR, European symbol;
2;1k;R-EU_R0805;R0805;R44, R82;RESISTOR, European symbol;
9;1µF;C-EUC0805;C0805;C5, C6, C7, C8, C12, C13, C17, MULTI-BUTTON-1:C1, MULTI-BUTTON-2:C1;CAPACITOR, European symbol;
1;220;R-EU_R0805;R0805;R43;RESISTOR, European symbol;
1;22k;R-EU_R0805;R0805;R11;RESISTOR, European symbol;
2;22µF;C-EUC0805;C0805;C11, C16;CAPACITOR, European symbol;
24;270;R-EU_R0805;R0805;R16, R18, R19, R21, R23, R25, R27, R29, R31, R33, R39, R41, R59, R60, R61, R62, R66, R67, R68, R69, R78, R79, R80, R81;RESISTOR, European symbol;
2;2k2;R-EU_R0805;R0805;MULTI-BUTTON-1:R2, MULTI-BUTTON-2:R2;RESISTOR, European symbol;
5;330;R-EU_R0805;R0805;R4, R5, R10, R13, R14;RESISTOR, European symbol;
2;470;R-EU_R0805;R0805;R1, R45;RESISTOR, European symbol;
1;4700µF;CPOL-EUTT5D11L;TT5D11L;C10;POLARIZED CAPACITOR, European symbol;
2;4k7;R-EU_R0805;R0805;MULTI-BUTTON-1:R1, MULTI-BUTTON-2:R1;RESISTOR, European symbol;
1;6k8;R-EU_R0805;R0805;R12;RESISTOR, European symbol;
4;BSS138;BSS123;SOT23;Q1, Q2, Q3, Q4;N-CHANNEL MOS FET;
1;DC-DC-CONVERTER;DC-DC-CONVERTER;DC-DC-CONVERTER;DC-DC-6V;;715-8575
1;DIODE_S15P45;DIODE_S15P45;TO-277A;D1;;
3;DYNAMIXEL-1X03AX;DYNAMIXEL-1X03AX;DYNAMIXEL_AX_1X03;AX12_D, AX12_G, AX12_G1;;
4;DYNAMIXEL-1X03XL;DYNAMIXEL-1X03XL;DYNAMIXEL_XL_1X03;XL320_D, XL320_G, XL320_G1, XL320_G2;;
1;JST-03;JST-03;GH-03-V;JUMPER;;
4;JST-04GH-V;JST-04GH-V;GH-04-V;ENCODEUR_DROIT, ENCODEUR_GAUCHE, GYRO, LIPO1;;
3;JST-05;JST-05;GH-05-V;DEL_GYRO, TOF_LP_D_AND_DISPLAY, TOF_LP_G;;
1;JST-06;JST-06;GH-06-V;TOF_PINCE;;
3;JST-10;JST-10;GH-10-V;GRUE, GRUE1, PHARES_ET_TOF_AV;;
2;JST-12;JST-12;GH-12-V;ARRET_URGENCE, LIPO;;
1;JST-15;JST-15;GH-15-V;DELS_ET_TOF_AR;;
5;L298;L298;MULTIWATT-15;H-BRIDGE1:IC1, H-BRIDGE_AR_D:IC1, H-BRIDGE_AR_G:IC1, H-BRIDGE_AV_D:IC1, H-BRIDGE_AV_G:IC1;DUAL FULL-BRIDGE DRIVER;
1;MF-LSMF300;MF-LSMF300;MF-LSMF300;F1;PolySwitch (TM) Resettable Device;817-1652
1;MF-MSMF110;MF-MSMF110;MF-MSMF110;F2;;647-8207
6;PUSH-BUTTON;PUSH-BUTTON;PUSH-BUTTON;MULTI-BUTTON-1:U1, MULTI-BUTTON-1:U2, MULTI-BUTTON-1:U3, MULTI-BUTTON-2:U1, MULTI-BUTTON-2:U2, MULTI-BUTTON-2:U3;;479-1491
2;PUSH-BUTTON;PUSH-BUTTON;PUSH-BUTTON;U$2, U$4;;479-1491
4;R-78C3.3-1.0;R-78C3.3-1.0;SIP3;DC1, DC2, DC5, DC7;INNOLINE DC/DC-Converter 1.0 AMP SIP3 Single Output;
2;R-78C5.0-1.0;R-78C5.0-1.0;SIP3;DC3, DC6;INNOLINE DC/DC-Converter 1.0 AMP SIP3 Single Output;
1;R-78C9.0-1.0;R-78C9.0-1.0;SIP3;DC4;INNOLINE DC/DC-Converter 1.0 AMP SIP3 Single Output;
2;REG1117;REG1117;SOT223;IC1, IC3;800mA and 1A Low Dropout (LDO) Positive Regulator;885-5432
1;RGEF800;RGEF800;5MM;P1;;517-6966
1;RPI-ZERO;RPI-ZERO;RASPBERRYPI_BASTELSTUBE_V13_RASPI_BOARD_B+_FULL;RPI;;
25;S1M;S1M;SMA;D2, H-BRIDGE1:D1, H-BRIDGE1:D2, H-BRIDGE1:D3, H-BRIDGE1:D4, H-BRIDGE1:D5, H-BRIDGE1:D6, H-BRIDGE1:D7, H-BRIDGE1:D8, H-BRIDGE_AR_D:D1, H-BRIDGE_AR_D:D2, H-BRIDGE_AR_D:D3, H-BRIDGE_AR_D:D4, H-BRIDGE_AR_G:D1, H-BRIDGE_AR_G:D2, H-BRIDGE_AR_G:D3, H-BRIDGE_AR_G:D4, H-BRIDGE_AV_D:D1, H-BRIDGE_AV_D:D2, H-BRIDGE_AV_D:D3, H-BRIDGE_AV_D:D4, H-BRIDGE_AV_G:D1, H-BRIDGE_AV_G:D2, H-BRIDGE_AV_G:D3, H-BRIDGE_AV_G:D4;;872-2874
1;TEENSY_3.1-3.2_DIL;TEENSY_3.1-3.2_DIL;TEENSY_3.0-3.2&LC_DIL;U2;Teensy 3.1 or 3.2 in a DIL Layout.;
1;TEENSY_3.1-3.2_DIL+4;TEENSY_3.1-3.2_DIL+4;TEENSY_3.0-3.2&LC_DIL+4;U$1;Teensy 3.1 and 3.2 in a DIL package with the inner 4 pins;
1;TEENSY_3.5_DIL+USB;TEENSY_3.5_DIL+USB;TEENSY_3.5_DIL+USB;U1;;
2;TL36PO;TL36PO;TL3XPO;S2, S3;TINY SWITCH ON - ON;913-9069
1;WIZ820IO;WIZ820IO;WIZ820;U$3;;
25;bleu;LED5MM;LED5MM;LED36, LED58, LED59, LED60, LED61, LED62, LED63, LED64, LED98, LED102, LED124, LED125, LED126, LED127, LED128, LED129, LED130, LED134, LED156, LED157, LED158, LED159, LED160, LED161, LED162;LED;
2;blue;LEDSMT1206;1206;LED1, LED5;LED;
1;green;LEDSMT1206;1206;LED2;LED;
24;jaune;LED5MM;LED5MM;LED34, LED51, LED52, LED53, LED54, LED55, LED56, LED57, LED100, LED117, LED118, LED119, LED120, LED121, LED122, LED123, LED132, LED149, LED150, LED151, LED152, LED153, LED154, LED155;LED;
24;orange;LED5MM;LED5MM;LED33, LED37, LED38, LED39, LED40, LED41, LED42, LED43, LED99, LED103, LED104, LED105, LED106, LED107, LED108, LED109, LED131, LED135, LED136, LED137, LED138, LED139, LED140, LED141;LED;
1;orange;LEDSMT1206;1206;LED3;LED;
2;red;LEDSMT1206;1206;LED4, LED6;LED;
25;vert;LED5MM;LED5MM;LED35, LED44, LED45, LED46, LED47, LED48, LED49, LED50, LED97, LED101, LED110, LED111, LED112, LED113, LED114, LED115, LED116, LED133, LED142, LED143, LED144, LED145, LED146, LED147, LED148;LED;
